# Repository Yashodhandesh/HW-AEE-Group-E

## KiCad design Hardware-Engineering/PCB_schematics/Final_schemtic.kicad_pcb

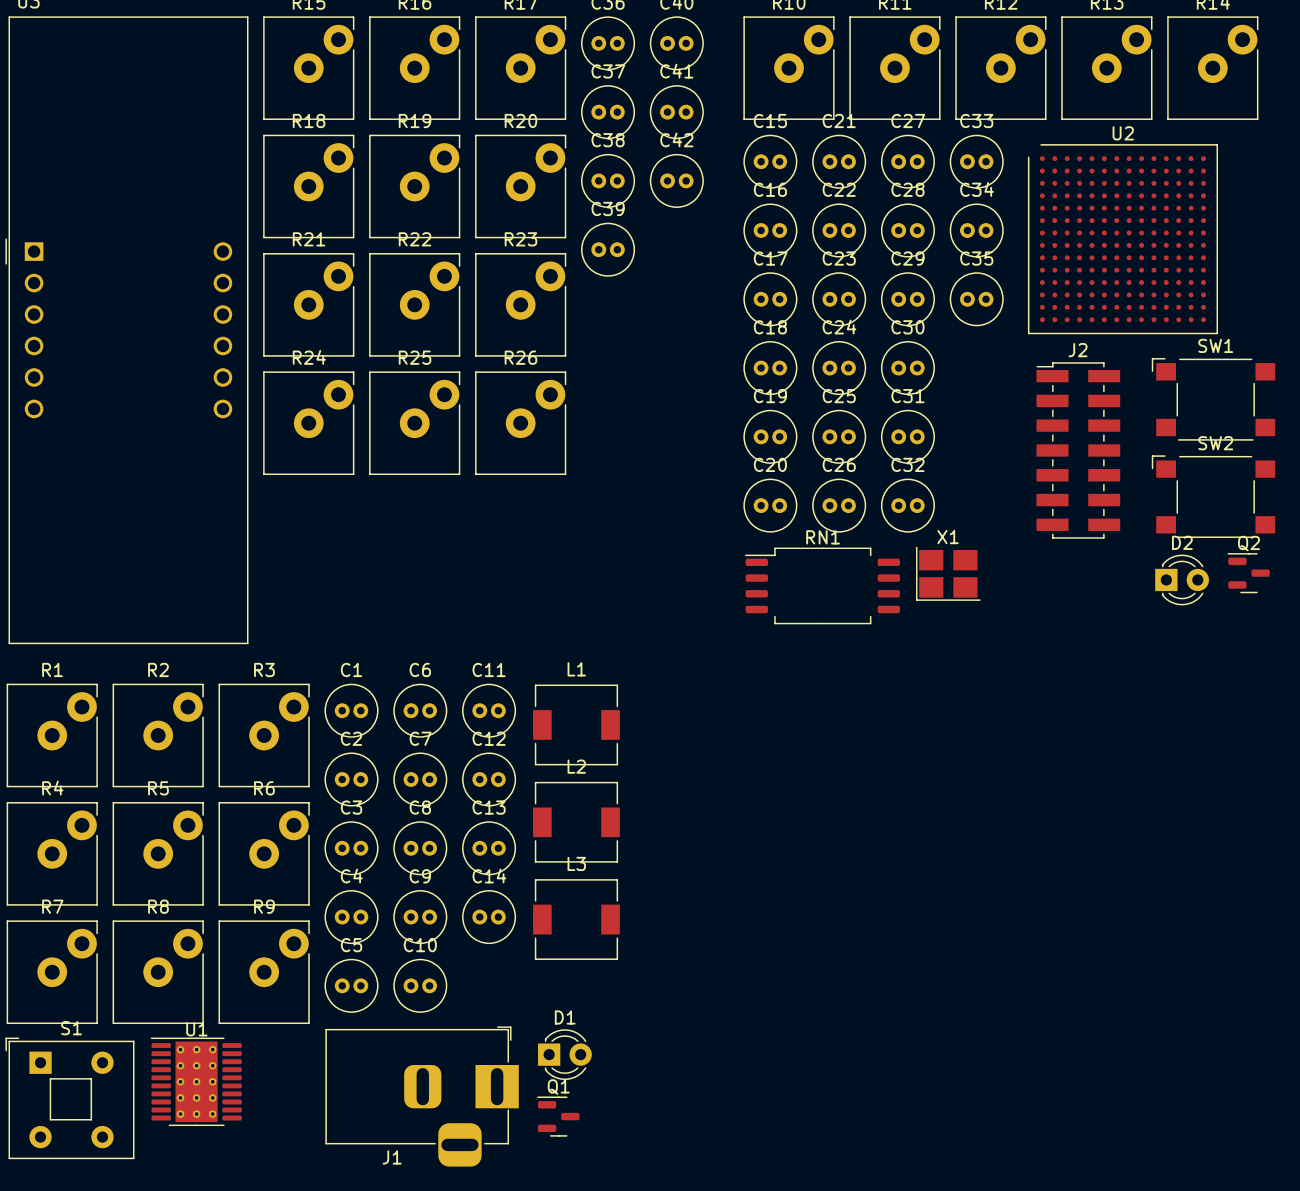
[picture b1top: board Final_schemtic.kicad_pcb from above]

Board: 4 copper layers, 85 parts (0 on the bottom side), 56 nets, no tracks yet.

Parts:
C1: 10u; C_Radial_D4.0mm_H5.0mm_P1.50mm
C2, C3: 10uf; C_Radial_D4.0mm_H5.0mm_P1.50mm
C4: 1uf; C_Radial_D4.0mm_H5.0mm_P1.50mm
C5, C6, C7: 0.1uf; C_Radial_D4.0mm_H5.0mm_P1.50mm
C8, C9, C10, C11, C12, C13, C14: 22uf; C_Radial_D4.0mm_H5.0mm_P1.50mm
C15, C17, C21, C36: 47uF; C_Radial_D4.0mm_H5.0mm_P1.50mm
C16, C18, C23, C24, C25, C26, C27, C28, C29, C30, C39, C40, C41, C42: 0.47uF; C_Radial_D4.0mm_H5.0mm_P1.50mm
C19, C20, C34: 0.1uF; C_Radial_D4.0mm_H5.0mm_P1.50mm
C22, C31, C32, C33, C37, C38: 4.7uF; C_Radial_D4.0mm_H5.0mm_P1.50mm
C35: 100uF; C_Radial_D4.0mm_H5.0mm_P1.50mm
D1, D2: LED_D3.0mm_FlatTop
J1: Barrel_Jack_Switch; BarrelJack_Horizontal
J2: XILINX_JTAG; PinHeader_2x07_P2.00mm_Vertical_SMD
L1, L2, L3: 2.2uH; L_6.3x6.3_H3
Q1, Q2: DMN2020L; SOT-23
R1: 100k; R_Radial_Power_L7.0mm_W8.0mm_Px2.40mm_Py2.30mm
R2, R3, R4: 2.2K; R_Radial_Power_L7.0mm_W8.0mm_Px2.40mm_Py2.30mm
R5, R9, R13: 680; R_Radial_Power_L7.0mm_W8.0mm_Px2.40mm_Py2.30mm
R6: 7.36K; R_Radial_Power_L7.0mm_W8.0mm_Px2.40mm_Py2.30mm
R7: 3.0K; R_Radial_Power_L7.0mm_W8.0mm_Px2.40mm_Py2.30mm
R8: 100K; R_Radial_Power_L7.0mm_W8.0mm_Px2.40mm_Py2.30mm
R10, R11, R14: 4.75K; R_Radial_Power_L7.0mm_W8.0mm_Px2.40mm_Py2.30mm
R12, R15, R16, R17, R18, R19, R20, R21, R22, R23, R24: 330; R_Radial_Power_L7.0mm_W8.0mm_Px2.40mm_Py2.30mm
R25, R26: R_Small; R_Radial_Power_L7.0mm_W8.0mm_Px2.40mm_Py2.30mm
RN1: 10K; SOIC-8_7.5x5.85mm_P1.27mm
S1: B3FS_1010P; SW_Push_2P1T_Toggle_CK_PVA1xxH1xxxxxxV2
SW1, SW2: SW_Omron_B3FS; SW_SPST_Omron_B3FS-100xP
U1: TPS65581; HTSSOP-20-1EP_4.4x6.5mm_P0.65mm_EP3.4x6.5mm_Mask2.75x3.43mm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
U2: XC7S50-FTGB196; Xilinx_FTGB196
U3: CA56-12CGKWA
X1: DSC61XX; Oscillator_SMD_Abracon_ASE-4Pin_3.2x2.5mm_HandSoldering

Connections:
+1V0: C10.2, C13.2, C14.2, C17.1, C22.1, C24.1, C26.1, C27.1, C28.1, C29.1, C30.1, C31.1, C32.1, C33.1, C35.1, L3.2, R5.2, U2.D6 (VCCINT), U2.D8 (VCCINT), U2.E5 (VCCBRAM), U2.E7 (VCCINT), U2.E9 (VCCINT), U2.F6 (VCCINT), U2.G5 (VCCBRAM), U2.G9 (VCCINT), U2.H6 (VCCINT), U2.J5 (VCCBRAM), U2.J9 (VCCINT), U2.K6 (VCCINT), U2.K8 (VCCINT)
+1V8: C15.1, C16.1, C18.1, C19.2, C20.1, C23.1, C25.1, U2.F8 (VCCADC_0), U2.F10 (VCCAUX), U2.H8 (VREFP_0), U2.H10 (VCCAUX), U2.K10 (VCCAUX), U2.L9 (VCCAUX)
+1V8A: C8.2, C11.2, L2.2, R7.2
+3V3: C9.2, C12.2, C21.1, C34.2, C36.2, C37.2, C38.2, C39.2, C40.2, C41.2, C42.2, D1.2 (A), D2.2 (A), J2.2 (VREF), L1.2, R6.2, R8.2, R10.1, R11.1, R12.2, R14.1, RN1.5 (R4.2), RN1.6 (R3.2), RN1.7 (R2.2), RN1.8 (R1.2), U2.G13 (VCCO_14), U2.K13 (VCCO_14), U2.M7 (M0_0), U2.N6 (VCCO_0), U2.N7 (CFGBVS_0), U2.N8 (VCCO_0), U2.N13 (VCCO_14), X1.1 (OE), X1.4 (VCC)
+12V: C1.2, C2.2, C3.2, J1.1, R1.1, U1.1 (VIN), U1.2 (VIN)
/Display/DSA: R15.2, U3.11 (a)
/Display/DSA_EN: R15.1, U2.E11 (IO_0_14)
/Display/DSB: R16.2, U3.7 (b)
/Display/DSB_EN: R16.1, U2.B11 (IO_L1P_T0_D00_MOSI_14)
/Display/DSC: R17.2, U3.4 (c)
/Display/DSCA1: R23.1, U3.12 (CA1)
/Display/DSCA1_EN: R23.2, U2.A13 (IO_L4N_T0_D05_14)
/Display/DSCA2: R24.1, U3.9 (CA2)
/Display/DSCA2_EN: R24.2, U2.B13 (IO_L5P_T0_D06_14)
/Display/DSCA3: R25.1, U3.8 (CA3)
/Display/DSCA3_EN: R25.2, U2.B14 (IO_L5N_T0_D07_14)
/Display/DSCA4: R26.1, U3.6 (CA4)
/Display/DSCA4_EN: R26.2, U2.C11 (IO_L6P_T0_FCS_B_14)
/Display/DSC_EN: R17.1, U2.B12 (IO_L1N_T0_D01_DIN_14)
/Display/DSD: R18.2, U3.2 (d)
/Display/DSD_EN: R18.1, U2.D10 (IO_L2P_T0_D02_14)
/Display/DSE: R19.2, U3.1 (e)
/Display/DSE_EN: R19.1, U2.C10 (IO_L2N_T0_D03_14)
/Display/DSF: R20.2, U3.10 (f)
/Display/DSF_EN: R20.1, U2.B10 (IO_L3P_T0_DQS_PUDC_B_14)
/Display/DSG: R21.2, U3.5 (g)
/Display/DSG_EN: R21.1, U2.A10 (IO_L3N_T0_DQS_EMCCLK_14)
/Display/DSP: R22.2, U3.3 (DPX)
/Display/DSP_EN: R22.1, U2.A12 (IO_L4P_T0_D04_14)
/FPGA/FPGA_DONE: Q2.1 (G), R12.1, U2.P9 (DONE_0)
/FPGA/INIT_B: R10.2, U2.P8 (INIT_B_0)
/FPGA/JTAG_TCK: J2.6 (TCK), RN1.2 (R2.1), U2.A7 (TCK_0)
/FPGA/JTAG_TDI: J2.10 (TDI), RN1.4 (R4.1), U2.P7 (TDI_0)
/FPGA/JTAG_TDO: J2.8 (TDO), RN1.3 (R3.1), U2.P6 (TDO_0)
/FPGA/JTAG_TMS: J2.4 (TMS), RN1.1 (R1.1), U2.M6 (TMS_0)
/FPGA/PROGRAM_B: R11.2, SW1.2, U2.L7 (PROGRAM_B_0)
/Power module/PGOOD: Q1.1 (G), R8.1, U1.7 (PG)
GND: C1.1, C2.1, C3.1, C4.1, C8.1, C9.1, C10.1, C11.1, C12.1, C13.1, C14.1, C15.2, C16.2, C17.2, C18.2, C19.1, C20.2, C21.2, C22.2, C23.2, C24.2, C25.2, C26.2, C27.2, C28.2, C29.2, C30.2, C31.2, C32.2, C33.2, C34.1, C35.2, C36.1, C37.1, C38.1, C39.1, C40.1, C41.1, C42.1, J1.2, J2.1 (GND), J2.3 (GND), J2.5 (GND), J2.7 (GND), J2.9 (GND), J2.11 (GND), J2.13 (GND), Q1.2 (S), Q2.2 (S), R2.1, R4.1, S1.1, S1.2, SW1.1, SW2.2, U1.5 (PGND1), U1.10 (GND), U1.18 (PGND2), U1.21 (PAD), U2.A1 (GND), U2.A6 (GND), U2.A9 (GND), U2.A11 (GND), U2.A14 (GND), U2.B4 (GND), U2.B7 (GND), U2.B8 (VCCBATT_0), U2.B9 (GND), U2.C2 (GND), U2.C6 (GND), U2.C7 (GND), U2.C8 (GND), U2.C9 (GND), U2.C13 (GND), U2.D5 (GND), U2.D7 (GND), U2.D9 (GND), U2.D11 (GND), U2.E1 (GND), U2.E3 (GND), U2.E6 (GND), U2.E8 (GND), U2.E10 (GND), U2.E14 (GND), U2.F5 (GND), U2.F7 (GNDADC_0), U2.F9 (GND), U2.G3 (GND), U2.G6 (GND), U2.G7 (VREFN_0), U2.G8 (VP_0), U2.G10 (GND), U2.G12 (GND), U2.H5 (GND), U2.H7 (VN_0), U2.H9 (GND), U2.J6 (GND), U2.J7 (DXN_0), U2.J8 (DXP_0), U2.J10 (GND), U2.K1 (GND), U2.K5 (GND), U2.K7 (GND), U2.K9 (GND), U2.K14 (GND), U2.L4 (GND), U2.L6 (GND), U2.L8 (GND), U2.L10 (GND), U2.L11 (GND), U2.M8 (M1_0), U2.M9 (M2_0), U2.N3 (GND), U2.N5 (GND), U2.N9 (GND), U2.N12 (GND), U2.P1 (GND), U2.P14 (GND), X1.2 (GND)
unnamed: D1.1 (K), R9.2
unnamed: D2.1 (K), R13.2
unnamed: Q1.3 (D), R9.1
unnamed: Q2.3 (D), R13.1
unnamed: R1.2, S1.3, S1.4, U1.8 (EN1), U1.13 (EN3), U1.17 (EN2)
unnamed: R3.1, U1.16 (PGND3)
unnamed: C6.2, L2.1, U1.4 (SW1)
unnamed: C7.2, L3.1, U1.19 (SW2)
unnamed: C5.2, L1.1, U1.15 (SW3)
unnamed: C6.1, U1.3 (VBST1)
unnamed: C7.1, U1.20 (VBST2)
unnamed: C5.1, U1.14 (VBST3)
unnamed: R4.2, R7.1, U1.9 (VFB1)
unnamed: R2.2, R5.1, U1.11 (VFB2)
unnamed: R3.2, R6.1, U1.12 (VFB3)
unnamed: C4.2, U1.6 (VREG5)
SYSCLK: U2.G11 (IO_L12P_T1_MRCC_14), X1.3 (OUT)
SYSRES: R14.2, SW2.1, U2.H11 (IO_L13P_T2_MRCC_14)

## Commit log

2023-04-28 Create Group members
2023-06-16 Update Group members
2023-06-19 Rename LCD_I2C.ino to Arduino_output_node_code.ino
2023-06-19 Rename heart_beat_sensor.ino to Arduino_input_node.ino
2023-06-19 Rename arduino_input_node.ino to arduino_input_node_code.ino
2023-07-14 Kicad
